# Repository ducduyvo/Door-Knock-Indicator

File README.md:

# Door Knock Indicator for the Hearing Impaired
The concept is to design a system that will detect a knock on the door of a person
that has difficulty hearing. It should then indicate in a very obvious way to the person
that there is a knock at their door. It should be considered usability and installation
of the device.

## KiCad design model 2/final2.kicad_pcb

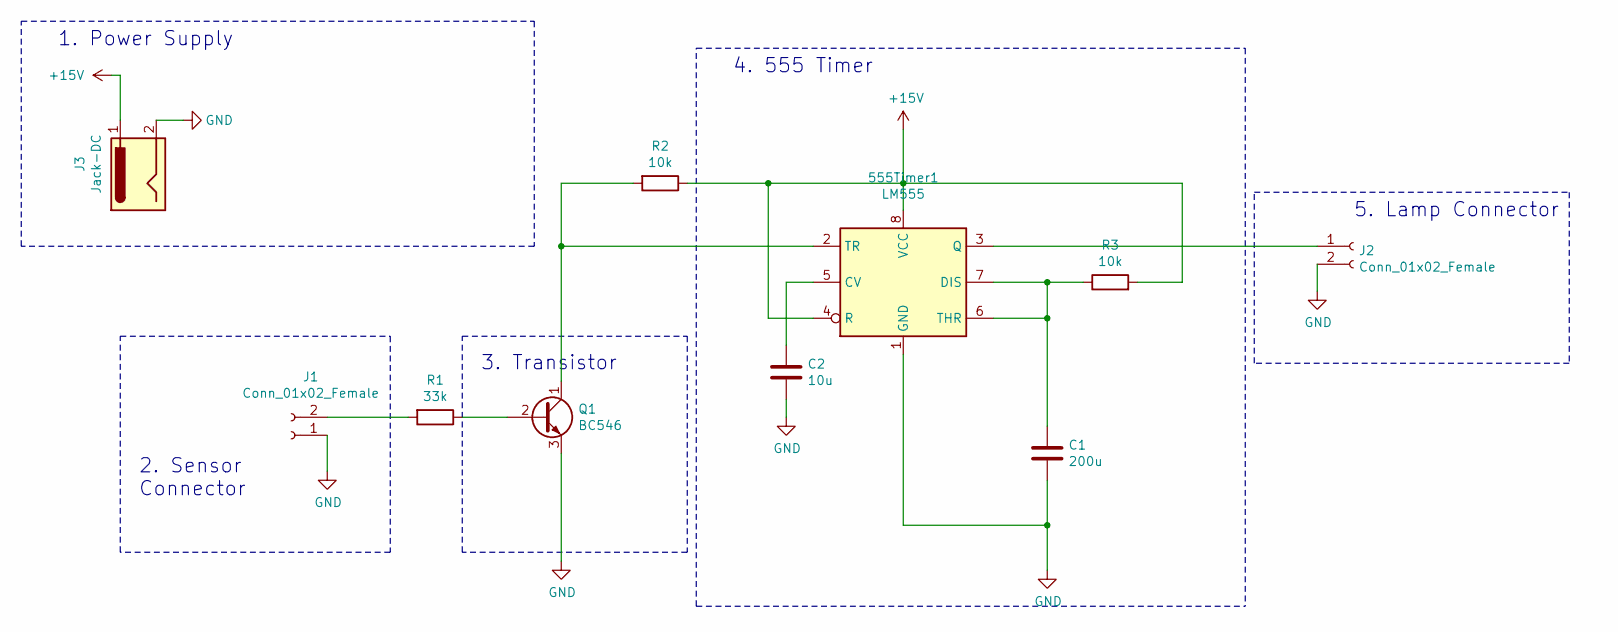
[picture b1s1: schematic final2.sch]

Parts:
555Timer1: LM555; DIP-8_W7.62mm
C1: 200u; C_0805_2012Metric_Pad1.15x1.40mm_HandSolder
C2: 10u; C_0805_2012Metric_Pad1.15x1.40mm_HandSolder
J1, J2: Conn_01x02_Female; AMASS_XT30U-F_1x02_P5.0mm_Vertical
J3: Jack-DC; BarrelJack_CUI_PJ-063AH_Horizontal
Q1: BC546; TO-92_Inline_Horizontal1
R1: 33k; R_0805_2012Metric_Pad1.15x1.40mm_HandSolder
R2, R3: 10k; R_0805_2012Metric_Pad1.15x1.40mm_HandSolder

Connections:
+15V: 555Timer1.4 (R), 555Timer1.8 (VCC), J3.1, R2.1, R3.2
GND: 555Timer1.1 (GND), C1.2, C2.2, J1.1, J2.2, J3.2, Q1.3 (E)
unnamed: 555Timer1.2 (TR), Q1.1 (C), R2.2
unnamed: 555Timer1.3 (Q), J2.1
unnamed: 555Timer1.5 (CV), C2.1
unnamed: 555Timer1.6 (THR), 555Timer1.7 (DIS), C1.1, R3.1
unnamed: J1.2, R1.2
unnamed: Q1.2 (B), R1.1

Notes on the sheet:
1. Power Supply
2. Sensor Connector
3. Transistor
4. 555 Timer
5. Lamp Connector

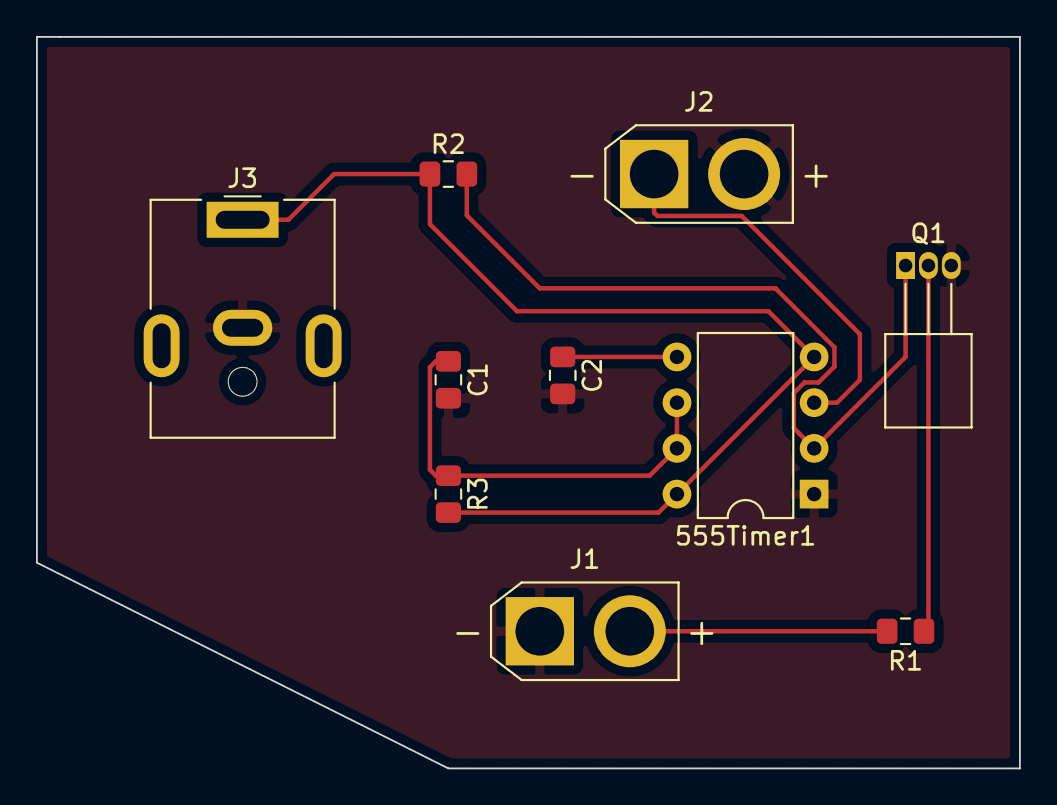
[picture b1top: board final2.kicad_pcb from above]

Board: 2 copper layers, 54.6 x 40.6 mm, 10 parts (0 on the bottom side), 8 nets.

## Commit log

2020-07-01 update all files
